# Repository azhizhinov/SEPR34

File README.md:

## SEPR34

The SEPR34 keyboard is a is a [Reviung34split](https://github.com/gtips/reviung/tree/master/reviung34split) fork with single ProMicro, hotswap socket and soldered-in switches support and little addition. The firmware is fully compatible.
This is a WIP.

## Parts
As for the parts list, you will need:
- 2x PCB (The left and right half are different)
- 34 MX or GLP keyswitches
- 34 MX keycaps (MX low-profile for the GLP)
- 34 Hotswap sockets for MX (optional)
- 2x [Ethernet sockets](https://aliexpress.com/item/32974903992.html)
- 1x ProMicro (Warning. I don't have possibility to test ALL clones, so, please, choose cearfully)

## Gerbers
You can find the Gerber files needed to order the PCB on the  directory. Look for the .zip of whatever version you would like!

## Attention
I'm a hobbyist/amateur at best. So there may be things that aren't optimized. So if you decide to use this, then please be advised that I'm not providing any sort of liability and you should exercise some caution. Use these file for your own risk. Thanks Sebastian Stumpf for this text.

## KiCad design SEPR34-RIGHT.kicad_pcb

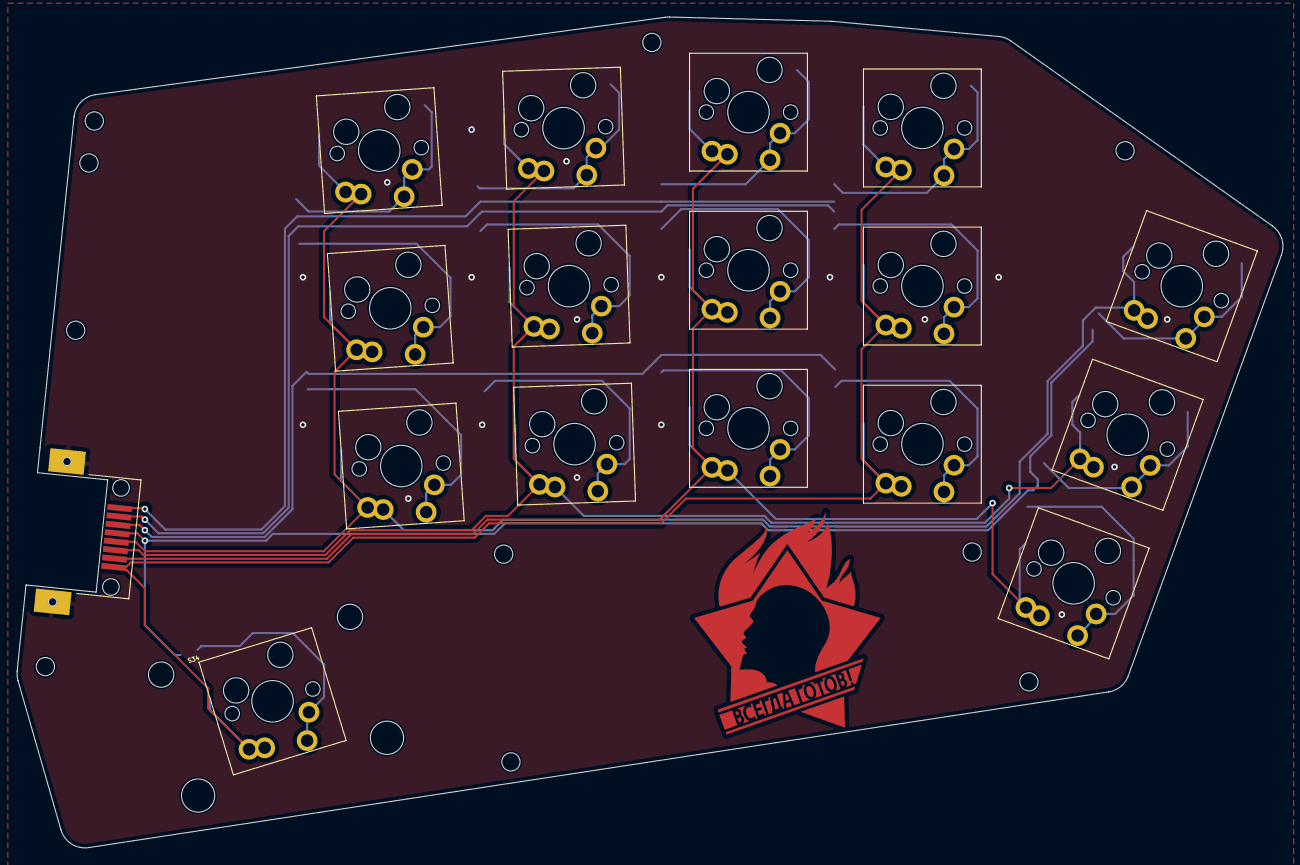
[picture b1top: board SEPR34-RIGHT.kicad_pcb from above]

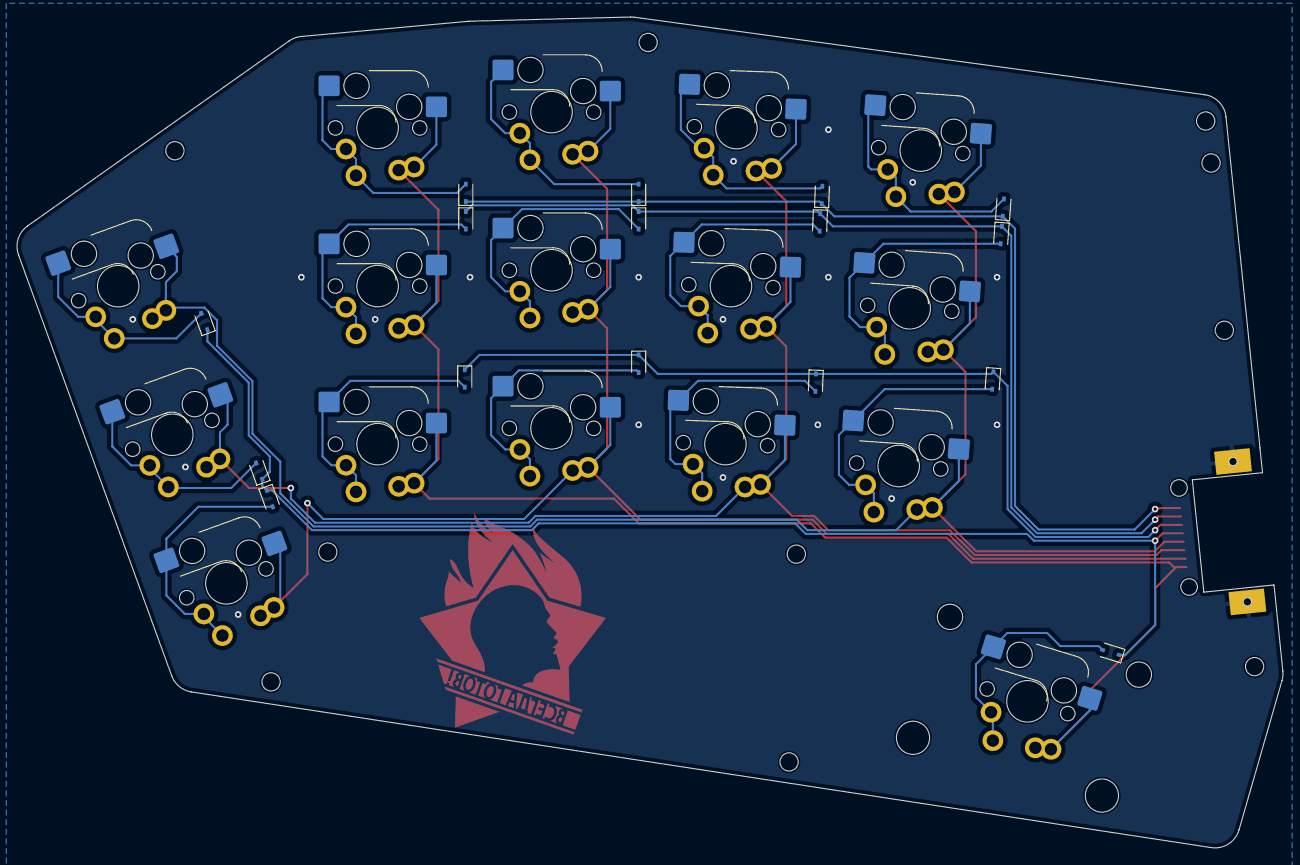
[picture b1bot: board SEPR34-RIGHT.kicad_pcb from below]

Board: 2 copper layers, 152.5 x 100.1 mm, 43 parts (16 on the bottom side), 24 nets.

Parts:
D19, D20, D21, D22, D23, D24, D25, D26, D27, D28, D29, D30, D31, D32, D33, D34: 1N4148; D_SOD-323
H1, H2, H3, H4, H5: MountingHole; MountingHole_2.2mm_M2
H?: MountingHole; MountingHole_2.2mm_M2
H?#2, H?#3, H?#4, H?#5: MountingHole; MountingHole_2.2mm_M2
J1: 8P8C; SEPOR-RJ45-SOCKET
S19, S20, S21, S22, S23, S24, S25, S26, S27, S28, S29, S30, S31, S32, S33: SWITCH; SEPOR-MX-KS27-HOTSWAP-1U
S34: SW_PUSH_2.0U; SEPOR-MX-KS27-HOTSWAP-2U

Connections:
unnamed: D19.2 (A), S19.2
unnamed: D20.2 (A), S20.2
unnamed: D21.2 (A), S21.2
unnamed: D22.2 (A), S22.2
unnamed: D23.2 (A), S23.2
unnamed: D24.2 (A), S24.2
unnamed: D25.2 (A), S25.2
unnamed: D26.2 (A), S26.2
unnamed: D27.2 (A), S27.2
unnamed: D28.2 (A), S28.2
unnamed: D29.2 (A), S29.2
unnamed: D30.2 (A), S30.2
unnamed: D31.2 (A), S31.2
unnamed: D32.2 (A), S32.2
unnamed: D33.2 (A), S33.2
unnamed: D34.2 (A), S34.2
col5: J1.5, S19.1, S23.1, S27.1, S31.1
col6: J1.6, S20.1, S24.1, S28.1, S32.1
col7: J1.7, S21.1, S25.1, S29.1, S33.1
col8: J1.8, S22.1, S26.1, S30.1, S34.1
row0: D19.1 (K), D20.1 (K), D21.1 (K), D22.1 (K), J1.1
row1: D23.1 (K), D24.1 (K), D25.1 (K), D26.1 (K), J1.2
row2: D27.1 (K), D28.1 (K), D29.1 (K), D30.1 (K), J1.3
row3: D31.1 (K), D32.1 (K), D33.1 (K), D34.1 (K), J1.4

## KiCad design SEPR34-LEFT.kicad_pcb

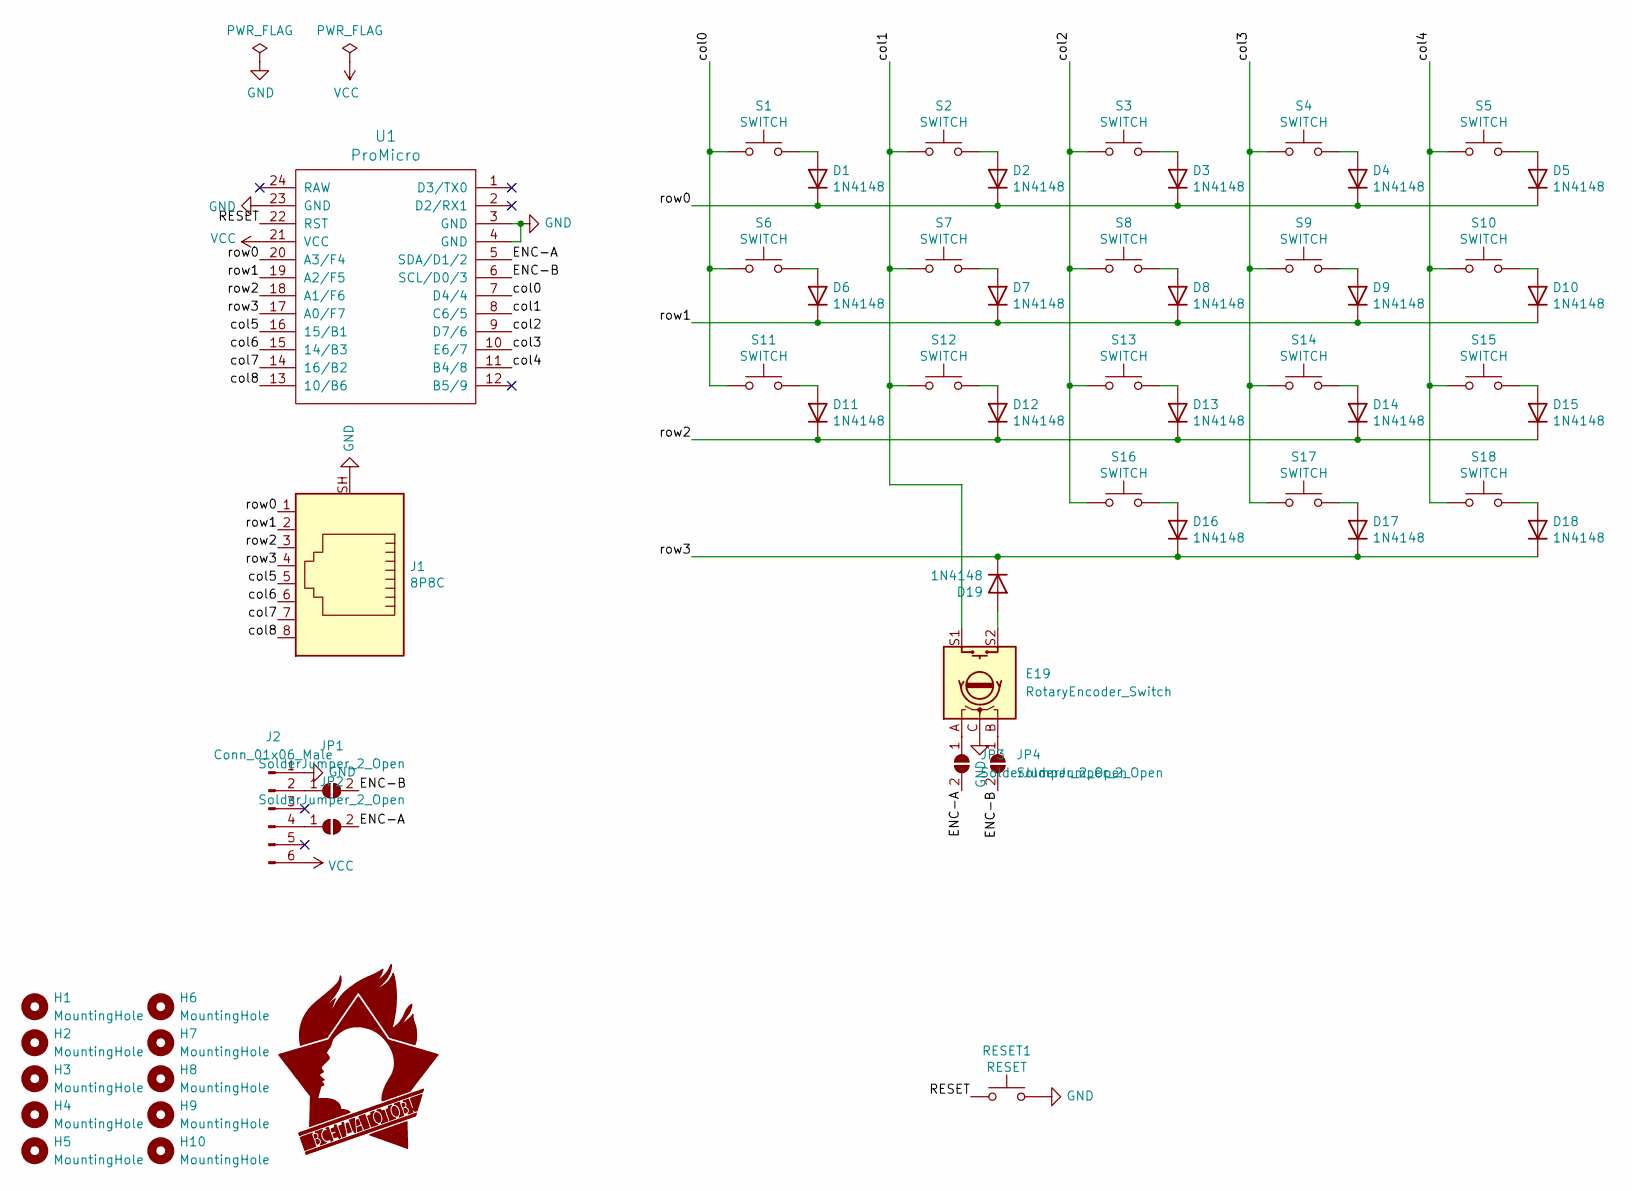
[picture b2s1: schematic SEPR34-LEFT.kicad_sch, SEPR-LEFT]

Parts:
D1, D2, D3, D4, D5, D6, D7, D8, D9, D10, D11, D12, D13, D14, D15, D16, D17, D18, D19: 1N4148; D_SOD-323
E19: RotaryEncoder_Switch; RotaryEncoder_Alps_EC11E-Switch_Vertical_H20mm
H1, H2, H3, H4, H5, H6, H7, H8, H9, H10: MountingHole; MountingHole_2.2mm_M2
J1: 8P8C; RJ45-HELING-MJ88-XX11-HLSV6-SMD
J2: Conn_01x06_Male; PinHeader_2x03_P2.00mm_Vertical
JP1, JP2, JP3, JP4: SolderJumper_2_Open; SolderJumper-2_P1.3mm_Open_TrianglePad1.0x1.5mm
RESET1: RESET; SW_SPST_TL3342
S1, S2, S3, S4, S5, S6, S7, S8, S9, S10, S11, S12, S13, S14, S15, S16, S17, S18: SWITCH; SEPOR-MX-KS27-HOTSWAP-1U
U1: ProMicro

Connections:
ENC-A: JP2.2 (B), JP3.2 (B), U1.5 (SDA/D1/2)
ENC-B: JP1.2 (B), JP4.2 (B), U1.6 (SCL/D0/3)
GND: E19.C, J1.SH, J2.1, RESET1.2, U1.3 (GND), U1.4 (GND), U1.23 (GND)
unnamed: D1.2 (A), S1.2
unnamed: D2.2 (A), S2.2
unnamed: D3.2 (A), S3.2
unnamed: D4.2 (A), S4.2
unnamed: D5.2 (A), S5.2
unnamed: D6.2 (A), S6.2
unnamed: D7.2 (A), S7.2
unnamed: D8.2 (A), S8.2
unnamed: D9.2 (A), S9.2
unnamed: D10.2 (A), S10.2
unnamed: D11.2 (A), S11.2
unnamed: D12.2 (A), S12.2
unnamed: D13.2 (A), S13.2
unnamed: D14.2 (A), S14.2
unnamed: D15.2 (A), S15.2
unnamed: D16.2 (A), S16.2
unnamed: D17.2 (A), S17.2
unnamed: D18.2 (A), S18.2
unnamed: D19.2 (A), E19.S2
unnamed: E19.A, JP3.1 (A)
unnamed: E19.B, JP4.1 (A)
unnamed: J2.2, JP1.1 (A)
unnamed: J2.4, JP2.1 (A)
VCC: J2.6, U1.21 (VCC)
col0: S1.1, S6.1, S11.1, U1.7 (D4/4)
col1: E19.S1, S2.1, S7.1, S12.1, U1.8 (C6/5)
col2: S3.1, S8.1, S13.1, S16.1, U1.9 (D7/6)
col3: S4.1, S9.1, S14.1, S17.1, U1.10 (E6/7)
col4: S5.1, S10.1, S15.1, S18.1, U1.11 (B4/8)
col5: J1.5, U1.16 (15/B1)
col6: J1.6, U1.15 (14/B3)
col7: J1.7, U1.14 (16/B2)
col8: J1.8, U1.13 (10/B6)
reset: RESET1.1, U1.22 (RST)
row0: D1.1 (K), D2.1 (K), D3.1 (K), D4.1 (K), D5.1 (K), J1.1, U1.20 (A3/F4)
row1: D6.1 (K), D7.1 (K), D8.1 (K), D9.1 (K), D10.1 (K), J1.2, U1.19 (A2/F5)
row2: D11.1 (K), D12.1 (K), D13.1 (K), D14.1 (K), D15.1 (K), J1.3, U1.18 (A1/F6)
row3: D16.1 (K), D17.1 (K), D18.1 (K), D19.1 (K), J1.4, U1.17 (A0/F7)

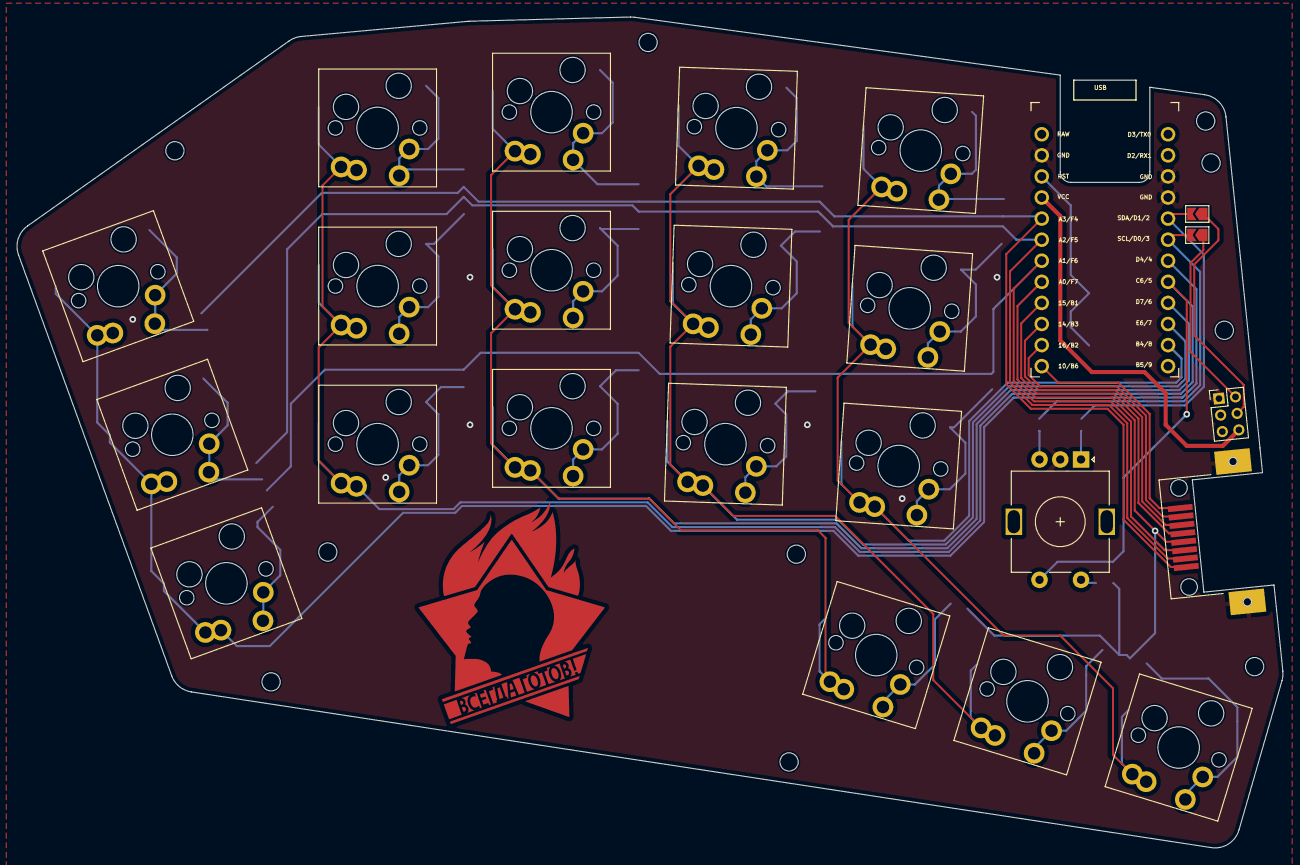
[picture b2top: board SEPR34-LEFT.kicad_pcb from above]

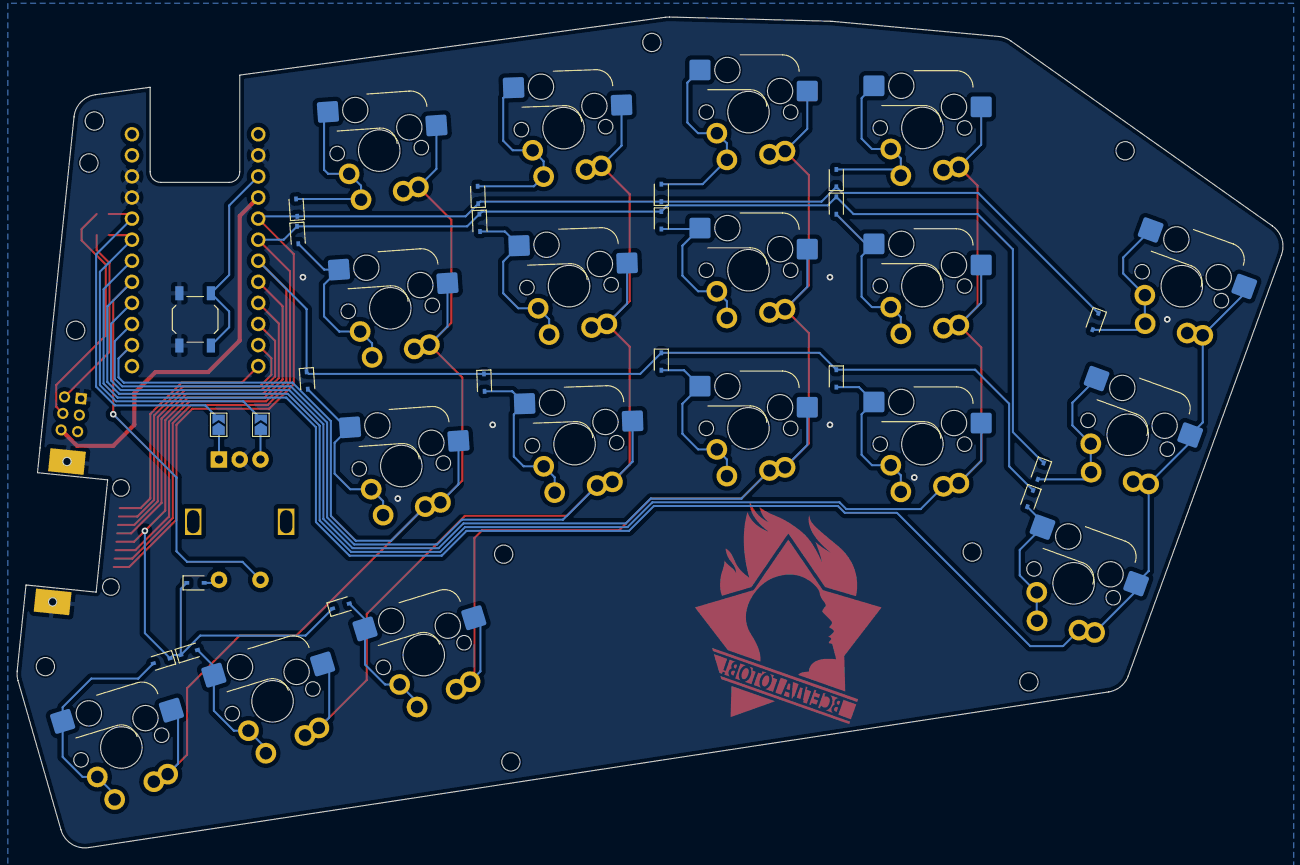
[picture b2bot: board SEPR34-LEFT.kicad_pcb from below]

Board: 2 copper layers, 152.5 x 100.1 mm, 56 parts (22 on the bottom side), 41 nets.
